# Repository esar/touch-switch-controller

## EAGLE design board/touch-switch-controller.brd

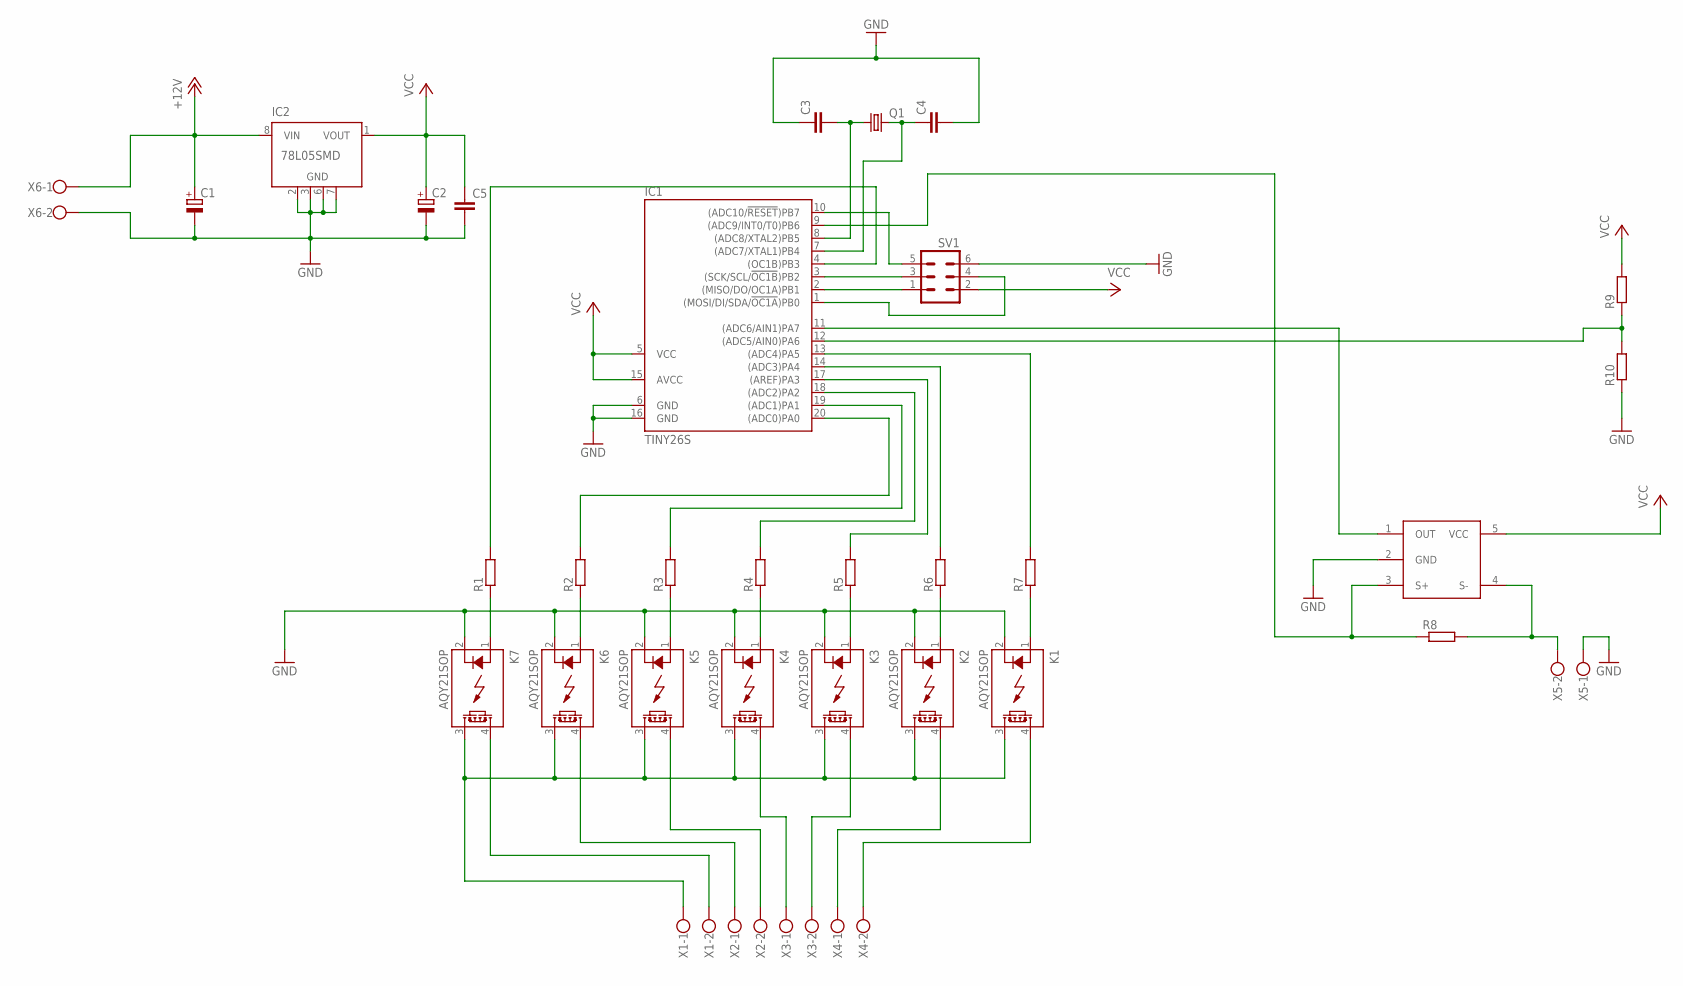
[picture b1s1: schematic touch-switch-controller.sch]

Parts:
C1, C2: CPOL-EUE3.5-8; E3,5-8
C3, C4, C5: C-EUC0603; C0603
IC1: TINY26S; SO20L
IC2: 78L05SMD; SO08
K1, K2, K3, K4, K5, K6, K7: AQY21SOP; SOP04
Q1: CRYSTALHC49UP; HC49UP
R1, R2, R3, R4, R5, R6, R7, R8, R9, R10: R-EU_R0603; R0603
SV1: MA03-2
U$1: ZXCT1086; SOT23-5L
X1, X2, X3, X4, X5, X6: W237-102

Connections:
+12V: C1.+, IC2.8 (VIN), X6.1
GND: C1.-, C2.-, C3.1, C4.2, C5.2, IC1.6 (GND), IC1.16 (GND), IC2.2 (GND), IC2.3 (GND), IC2.6 (GND), IC2.7 (GND), K1.2 (K), K2.2 (K), K3.2 (K), K4.2 (K), K5.2 (K), K6.2 (K), K7.2 (K), R10.1, SV1.6, U$1.2 (GND), X5.1, X6.2
unnamed: IC1.12 ((ADC5/AIN0)PA6), R9.1, R10.2
unnamed: IC1.13 ((ADC4)PA5), R7.2
unnamed: IC1.4 ((OC1B)PB3), R1.2
unnamed: IC1.20 ((ADC0)PA0), R2.2
unnamed: IC1.19 ((ADC1)PA1), R3.2
unnamed: IC1.9 ((ADC9/INT0/T0)PB6), R8.1, U$1.3 (S+)
unnamed: IC1.17 ((AREF)PA3), R5.2
unnamed: IC1.2 ((MISO/DO/OC1A)PB1), SV1.1
unnamed: IC1.3 ((SCK/SCL/!OC1B!)PB2), SV1.3
unnamed: IC1.10 ((ADC10/!RESET!)PB7), SV1.5
unnamed: IC1.1 ((MOSI/DI/SDA/!OC1A!)PB0), SV1.4
unnamed: K7.4 (DS1), X1.2
unnamed: K7.1 (A), R1.1
unnamed: K6.4 (DS1), X2.1
unnamed: K5.4 (DS1), X2.2
unnamed: K4.4 (DS1), X3.1
unnamed: K6.1 (A), R2.1
unnamed: K5.1 (A), R3.1
unnamed: K4.1 (A), R4.1
unnamed: K3.1 (A), R5.1
unnamed: K2.1 (A), R6.1
unnamed: K1.1 (A), R7.1
unnamed: K3.4 (DS1), X3.2
unnamed: K2.4 (DS1), X4.1
unnamed: K1.4 (DS1), X4.2
unnamed: K1.3 (DS2), K2.3 (DS2), K3.3 (DS2), K4.3 (DS2), K5.3 (DS2), K6.3 (DS2), K7.3 (DS2), X1.1
unnamed: R8.2, U$1.4 (S-), X5.2
unnamed: IC1.11 ((ADC6/AIN1)PA7), U$1.1 (OUT)
unnamed: C3.2, IC1.8 ((ADC8/XTAL2)PB5), Q1.1
unnamed: C4.1, IC1.7 ((ADC7/XTAL1)PB4), Q1.2
unnamed: IC1.18 ((ADC2)PA2), R4.2
unnamed: IC1.14 ((ADC3)PA4), R6.2
VCC: C2.+, C5.1, IC1.5 (VCC), IC1.15 (AVCC), IC2.1 (VOUT), R9.2, SV1.2, U$1.5 (VCC)

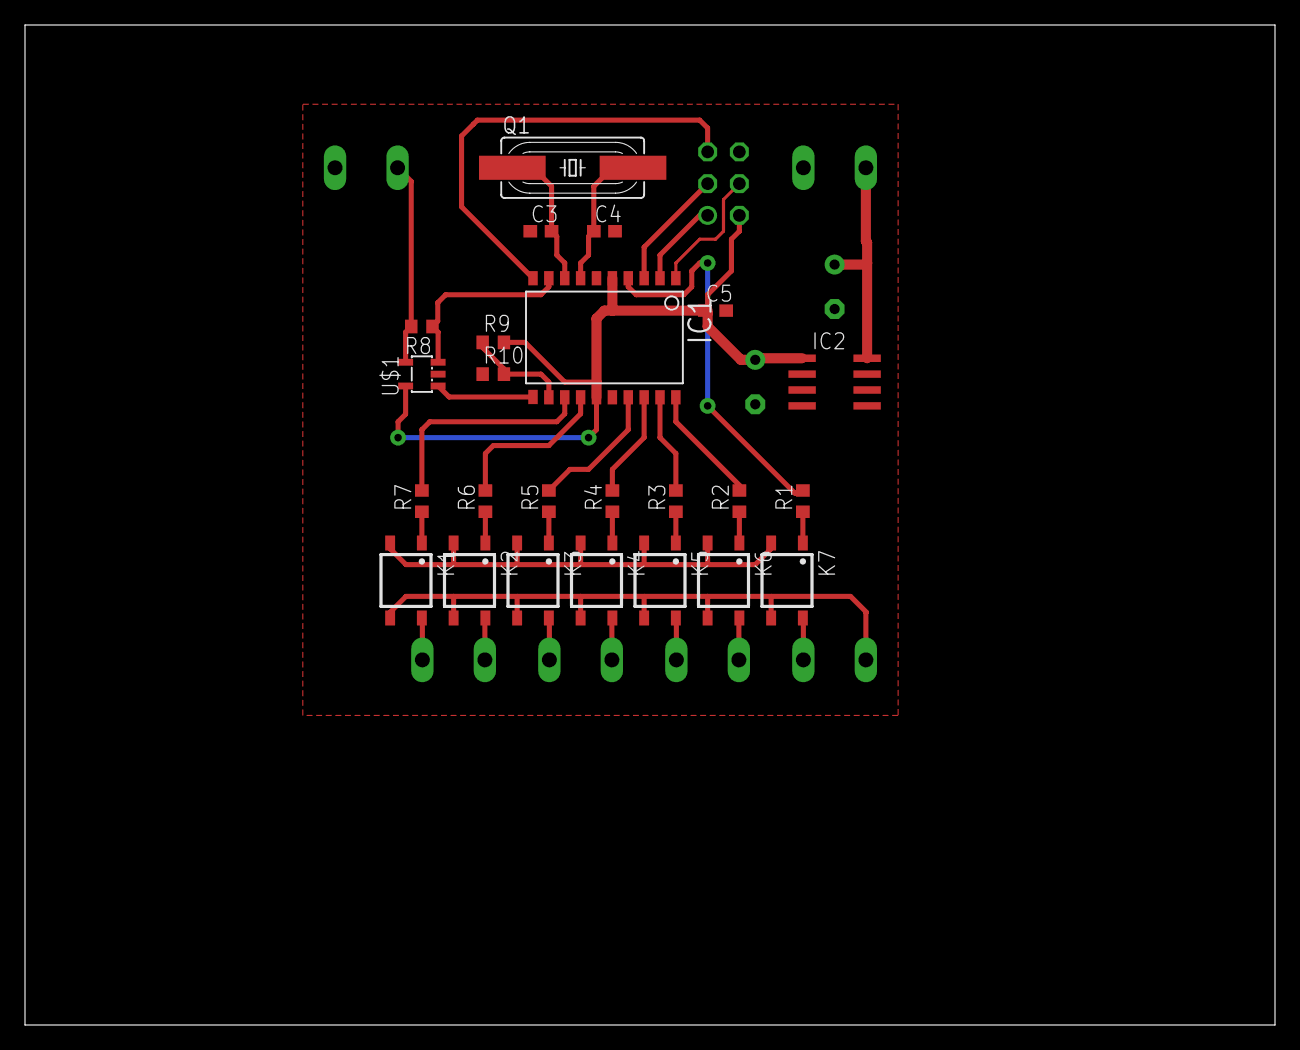
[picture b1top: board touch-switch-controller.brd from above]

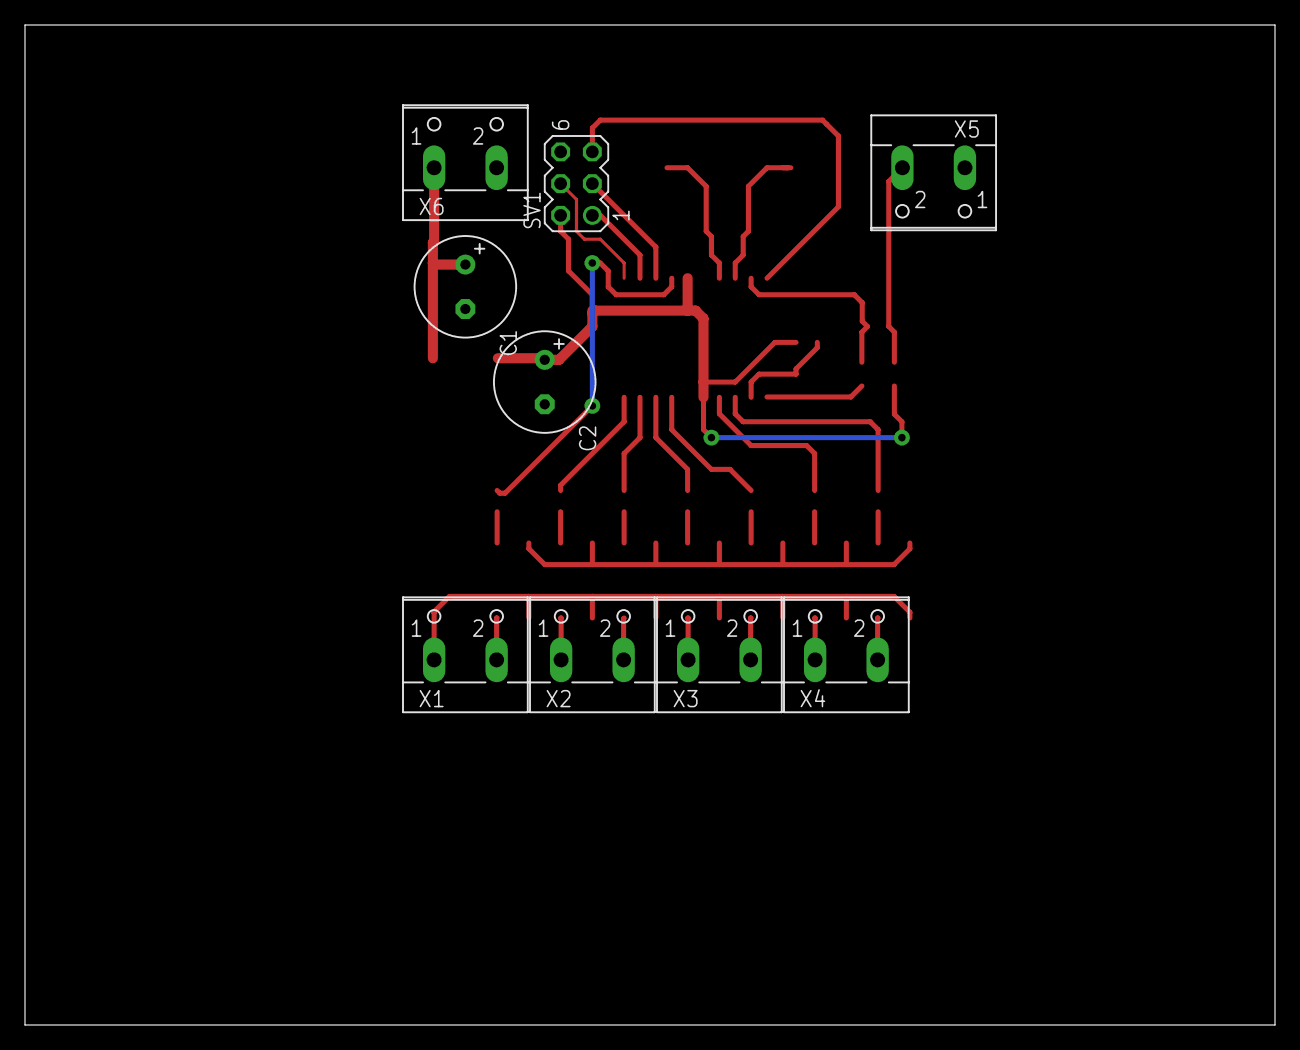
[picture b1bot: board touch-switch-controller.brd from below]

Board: 2 copper layers, 100.0 x 80.0 mm, 33 parts (9 on the bottom side), 35 nets.

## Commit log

2013-12-07 Initial import
